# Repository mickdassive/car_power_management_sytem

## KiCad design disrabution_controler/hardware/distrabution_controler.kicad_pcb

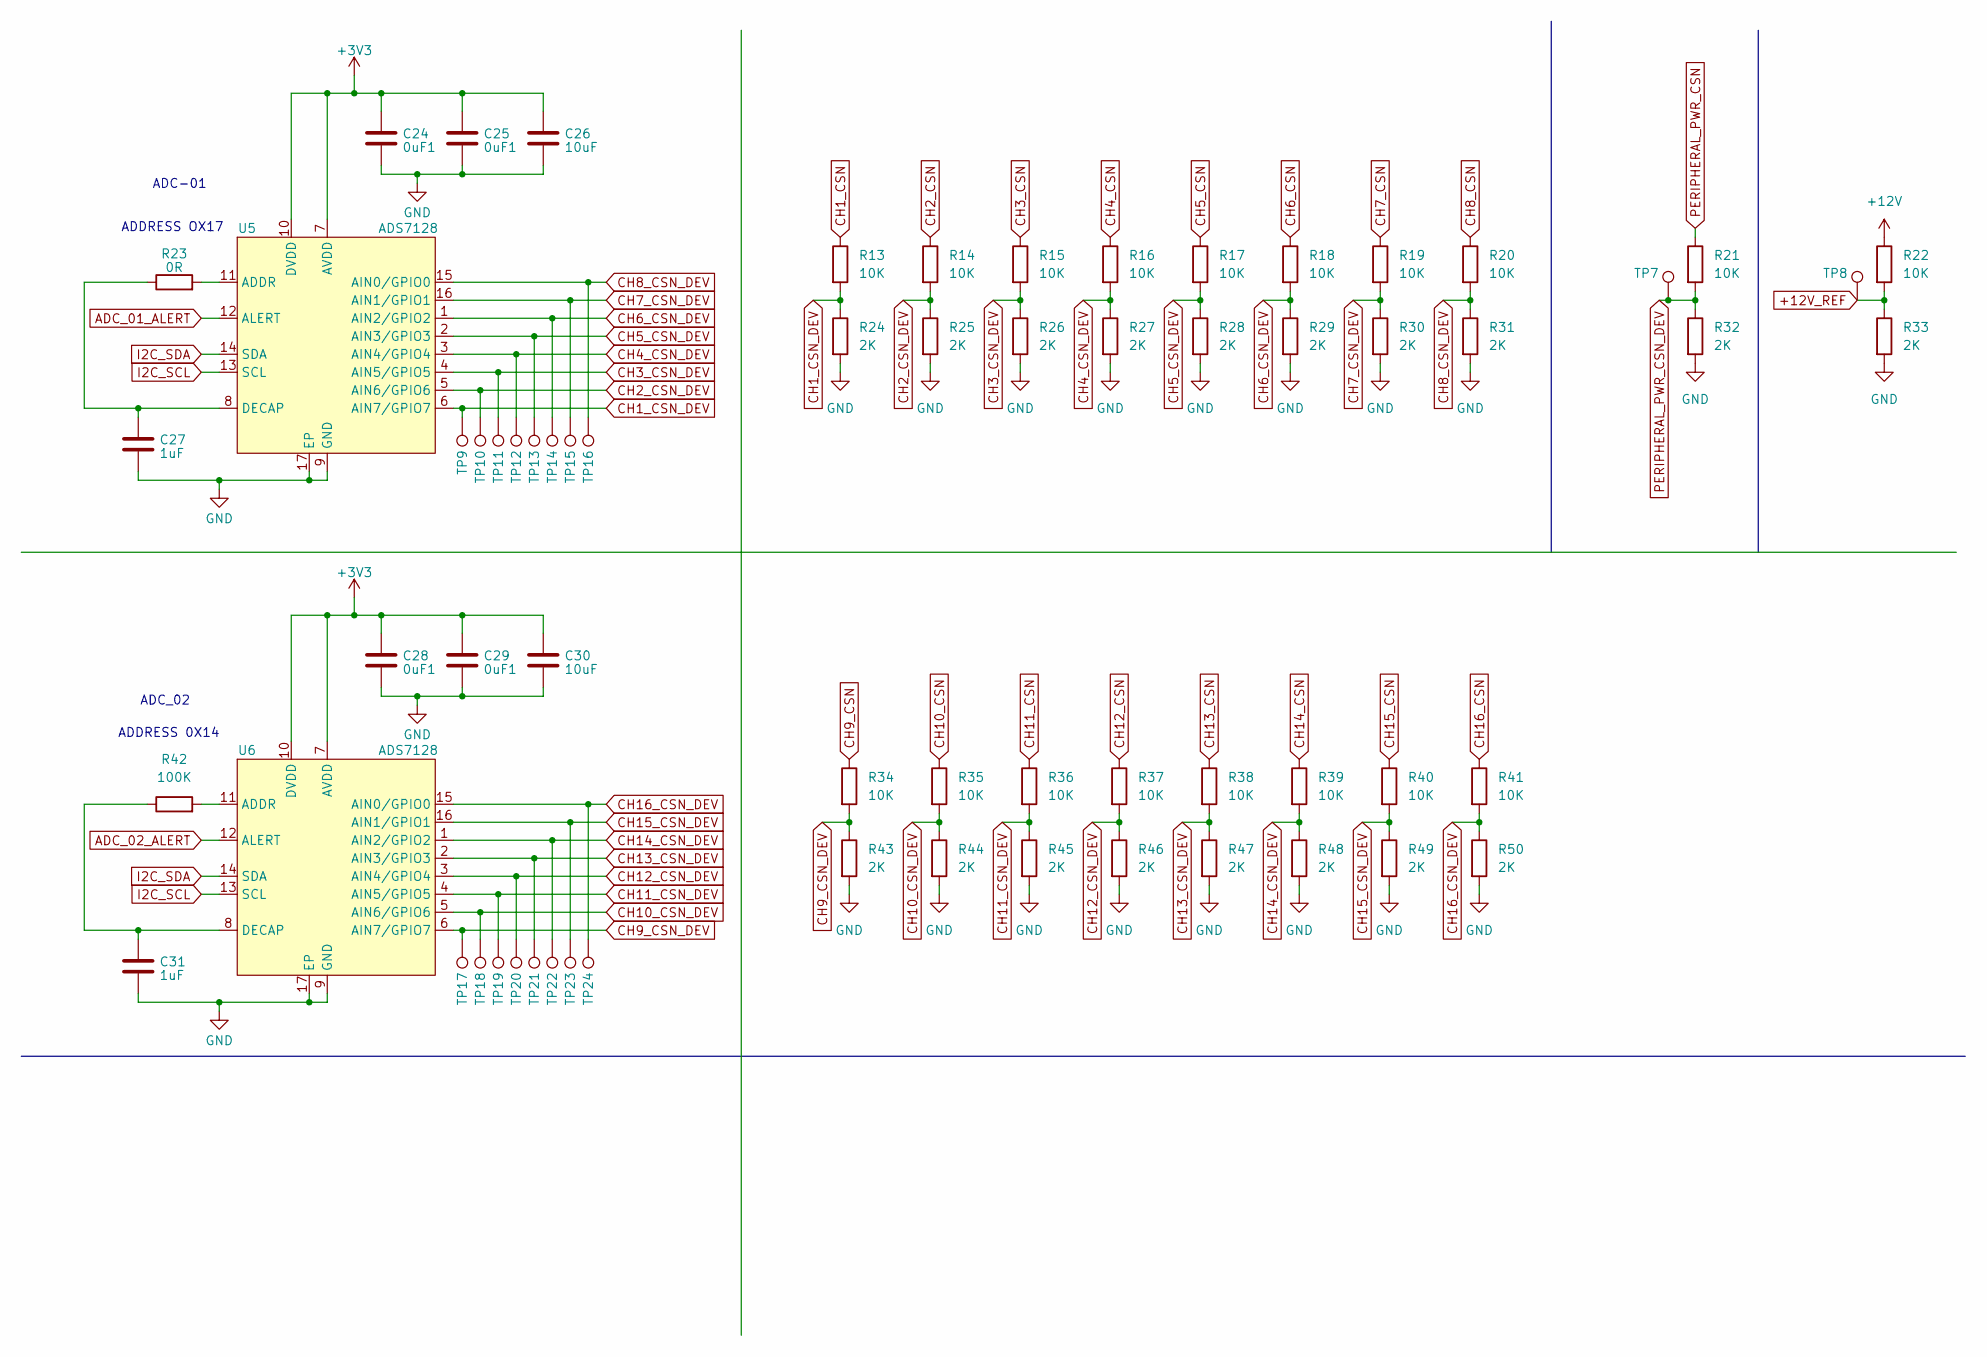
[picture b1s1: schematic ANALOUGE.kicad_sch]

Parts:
C24, C25, C28, C29: 0uF1; C_0603_1608Metric; Digikey Part Number 399-C0603C104M5RACTUCT-ND
C26, C30: 10uF; C_0603_1608Metric; Digikey Part Number 1276-1038-1-ND
C27, C31: 1uF; C_0603_1608Metric; Digikey Part Number 1276-1946-1-ND
R13, R14, R15, R16, R17, R18, R19, R20, R21, R22, R34, R35, R36, R37, R38, R39, R40, R41: 10K; R_0603_1608Metric; Digikey Part Number RMCF0603JT10K0CT-ND
R23: 0R; R_0603_1608Metric; Digikey Part Number 541-0.0GCT-ND
R24, R25, R26, R27, R28, R29, R30, R31, R32, R33, R43, R44, R45, R46, R47, R48, R49, R50: 2K; R_0603_1608Metric; Digikey Part Number 311-20.0KHRCT-ND
R42: 100K; R_0603_1608Metric; Digikey Part Number 541-100KHCT-ND
TP7, TP8, TP9, TP10, TP11, TP12, TP13, TP14, TP15, TP16, TP17, TP18, TP19, TP20, TP21, TP22, TP23, TP24: TestPoint_Pad_D1.0mm
U5, U6: ADS7128; WQFN-16-1EP_3x3mm_P0.5mm_EP1.6x1.6mm_ThermalVias; Digikey Part Number 296-ADS7128IRTERCT-ND

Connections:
+3V3: C24.1, C25.1, C26.1, C28.1, C29.1, C30.1, U5.7 (AVDD), U5.10 (DVDD), U6.7 (AVDD), U6.10 (DVDD); also elsewhere on the board
+12V: R22.1; also elsewhere on the board
+12V_REF: R22.2, R33.1, TP8.1; also elsewhere on the board
ADC_01_ALERT: U5.12 (ALERT); also elsewhere on the board
ADC_02_ALERT: U6.12 (ALERT); also elsewhere on the board
CH1_CSN: R13.1; also elsewhere on the board
CH1_CSN_DEV: R13.2, R24.1, TP9.1, U5.6 (AIN7/GPIO7)
CH2_CSN: R14.1; also elsewhere on the board
CH2_CSN_DEV: R14.2, R25.1, TP10.1, U5.5 (AIN6/GPIO6)
CH3_CSN: R15.1; also elsewhere on the board
CH3_CSN_DEV: R15.2, R26.1, TP11.1, U5.4 (AIN5/GPIO5)
CH4_CSN: R16.1; also elsewhere on the board
CH4_CSN_DEV: R16.2, R27.1, TP12.1, U5.3 (AIN4/GPIO4)
CH5_CSN: R17.1; also elsewhere on the board
CH5_CSN_DEV: R17.2, R28.1, TP13.1, U5.2 (AIN3/GPIO3)
CH6_CSN: R18.1; also elsewhere on the board
CH6_CSN_DEV: R18.2, R29.1, TP14.1, U5.1 (AIN2/GPIO2)
CH7_CSN: R19.1; also elsewhere on the board
CH7_CSN_DEV: R19.2, R30.1, TP15.1, U5.16 (AIN1/GPIO1)
CH8_CSN: R20.1; also elsewhere on the board
CH8_CSN_DEV: R20.2, R31.1, TP16.1, U5.15 (AIN0/GPIO0)
CH9_CSN: R34.1; also elsewhere on the board
CH9_CSN_DEV: R34.2, R43.1, TP17.1, U6.6 (AIN7/GPIO7)
CH10_CSN: R35.1; also elsewhere on the board
CH10_CSN_DEV: R35.2, R44.1, TP18.1, U6.5 (AIN6/GPIO6)
CH11_CSN: R36.1; also elsewhere on the board
CH11_CSN_DEV: R36.2, R45.1, TP19.1, U6.4 (AIN5/GPIO5)
CH12_CSN: R37.1; also elsewhere on the board
CH12_CSN_DEV: R37.2, R46.1, TP20.1, U6.3 (AIN4/GPIO4)
CH13_CSN: R38.1; also elsewhere on the board
CH13_CSN_DEV: R38.2, R47.1, TP21.1, U6.2 (AIN3/GPIO3)
CH14_CSN: R39.1; also elsewhere on the board
CH14_CSN_DEV: R39.2, R48.1, TP22.1, U6.1 (AIN2/GPIO2)
CH15_CSN: R40.1; also elsewhere on the board
CH15_CSN_DEV: R40.2, R49.1, TP23.1, U6.16 (AIN1/GPIO1)
CH16_CSN: R41.1; also elsewhere on the board
CH16_CSN_DEV: R41.2, R50.1, TP24.1, U6.15 (AIN0/GPIO0)
GND: C24.2, C25.2, C26.2, C27.2, C28.2, C29.2, C30.2, C31.2, R24.2, R25.2, R26.2, R27.2, R28.2, R29.2, R30.2, R31.2, R32.2, R33.2, R43.2, R44.2, R45.2, R46.2, R47.2, R48.2, R49.2, R50.2, U5.9 (GND), U5.17 (EP), U6.9 (GND), U6.17 (EP); also elsewhere on the board
I2C_SCL: U5.13 (SCL), U6.13 (SCL); also elsewhere on the board
I2C_SDA: U5.14 (SDA), U6.14 (SDA); also elsewhere on the board
unnamed: R23.2, U5.11 (ADDR)
unnamed: C27.1, R23.1, U5.8 (DECAP)
unnamed: R42.2, U6.11 (ADDR)
unnamed: C31.1, R42.1, U6.8 (DECAP)
PERIPHERAL_PWR_CSN: R21.1; also elsewhere on the board
PERIPHERAL_PWR_CSN_DEV: R21.2, R32.1, TP7.1; also elsewhere on the board

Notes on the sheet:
ADDRESS OX17
ADC_02
ADC-01
ADDRESS 0X14

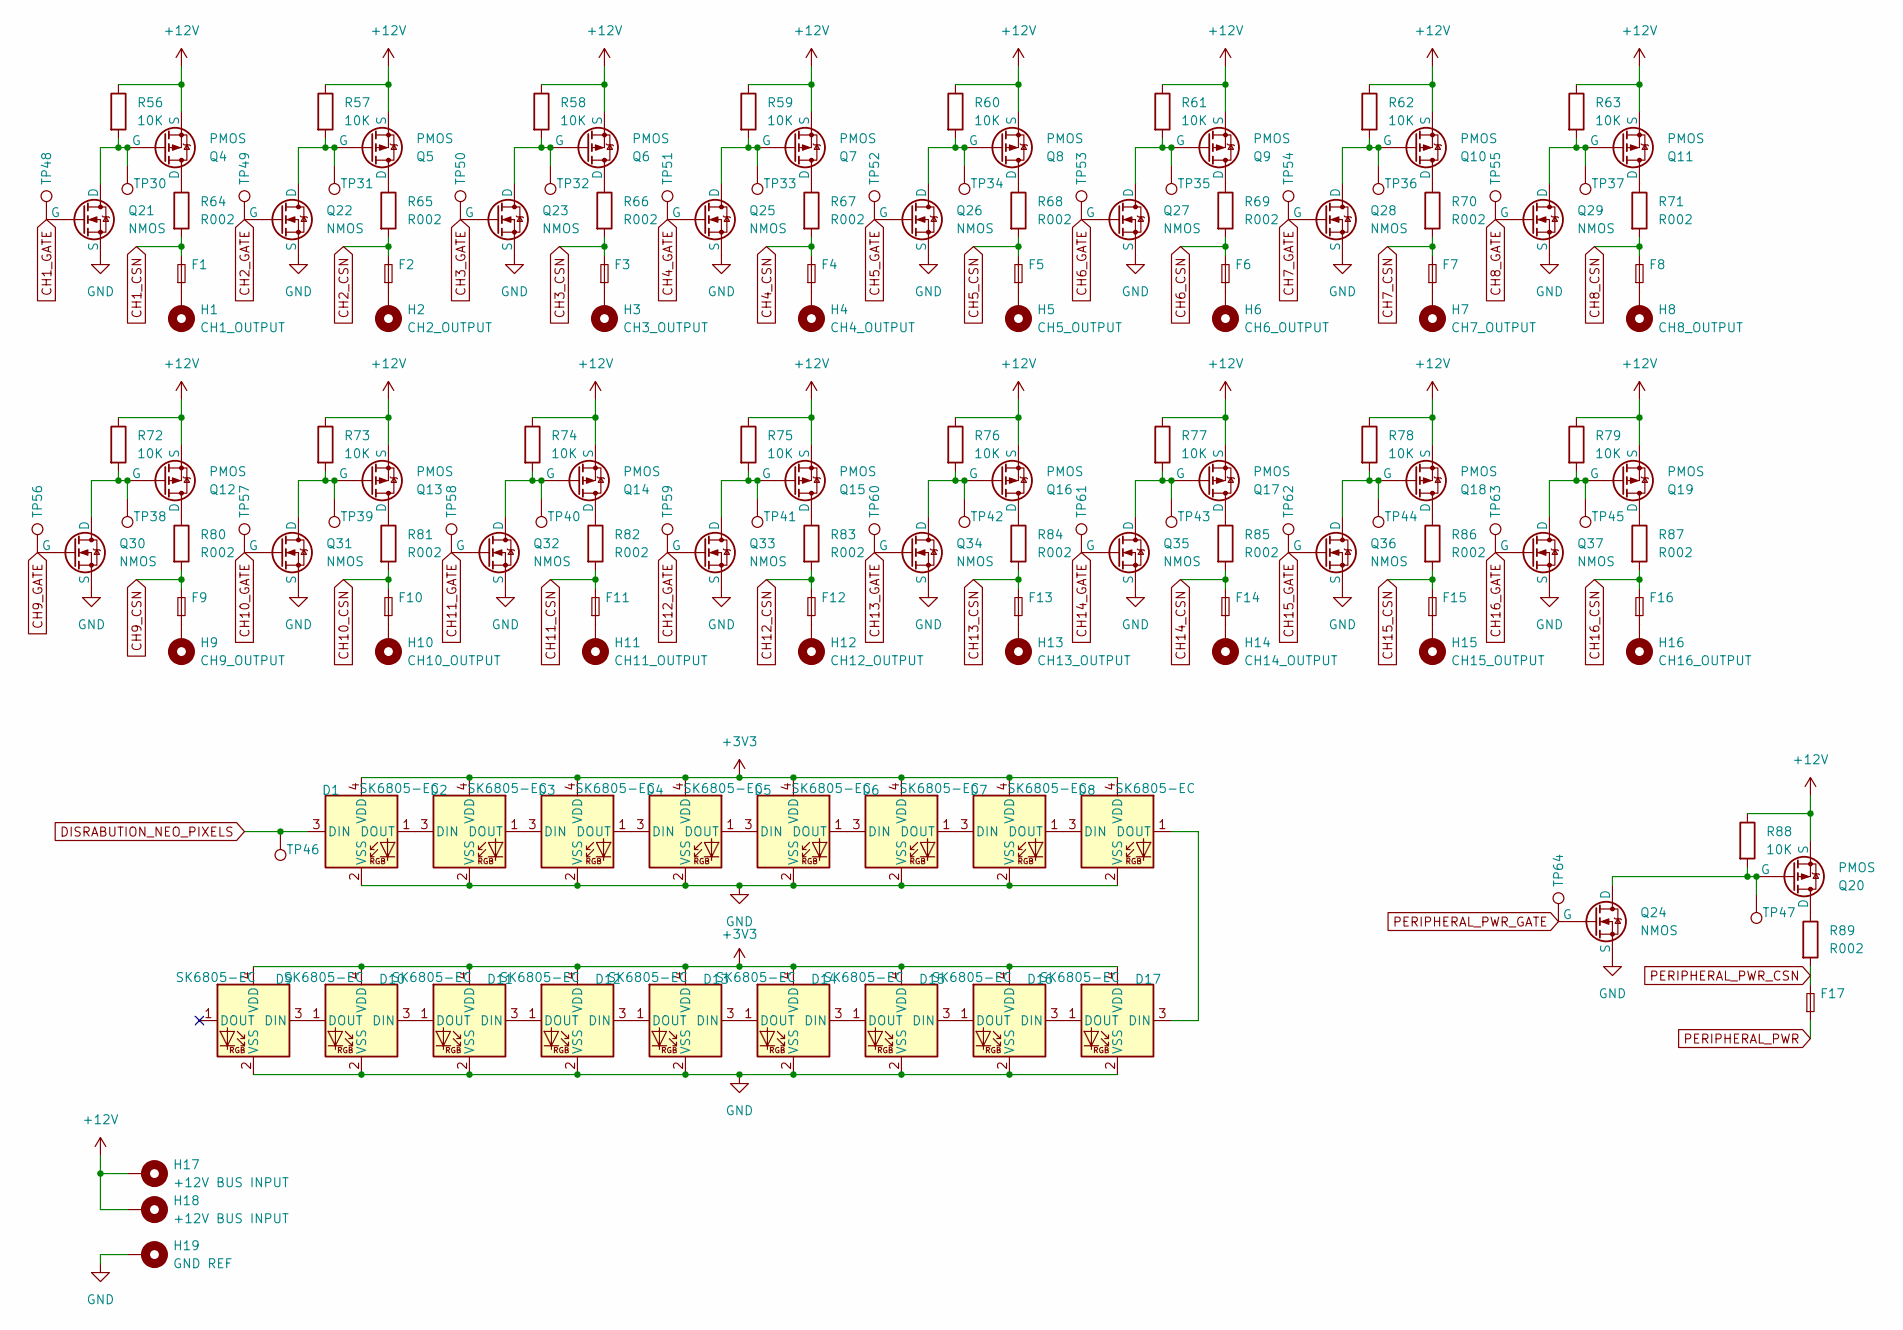
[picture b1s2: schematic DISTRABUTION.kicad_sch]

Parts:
D1, D2, D3, D4, D5, D6, D7, D8, D9, D10, D11, D12, D13, D14, D15, D16, D17: SK6805-EC; LED_SK6805_PLCC4_2.4x2.7mm_P1.3mm; Digikey Part Number 1528-4492-ND
F1, F2, F3, F4, F5, F6, F7, F8, F9, F10, F11, F12, F13, F14, F15, F16, F17: ATO_FUSEHOLDER; Digikey Part Number 36-3522-ND
H1: CH1_OUTPUT; MountingHole_6.4mm_M6_Pad_TopOnly
H2: CH2_OUTPUT; MountingHole_6.4mm_M6_Pad_TopOnly
H3: CH3_OUTPUT; MountingHole_6.4mm_M6_Pad_TopOnly
H4: CH4_OUTPUT; MountingHole_6.4mm_M6_Pad_TopOnly
H5: CH5_OUTPUT; MountingHole_6.4mm_M6_Pad_TopOnly
H6: CH6_OUTPUT; MountingHole_6.4mm_M6_Pad_TopOnly
H7: CH7_OUTPUT; MountingHole_6.4mm_M6_Pad_TopOnly
H8: CH8_OUTPUT; MountingHole_6.4mm_M6_Pad_TopOnly
H9: CH9_OUTPUT; MountingHole_6.4mm_M6_Pad_TopOnly
H10: CH10_OUTPUT; MountingHole_6.4mm_M6_Pad_TopOnly
H11: CH11_OUTPUT; MountingHole_6.4mm_M6_Pad_TopOnly
H12: CH12_OUTPUT; MountingHole_6.4mm_M6_Pad_TopOnly
H13: CH13_OUTPUT; MountingHole_6.4mm_M6_Pad_TopOnly
H14: CH14_OUTPUT; MountingHole_6.4mm_M6_Pad_TopOnly
H15: CH15_OUTPUT; MountingHole_6.4mm_M6_Pad_TopOnly
H16: CH16_OUTPUT; MountingHole_6.4mm_M6_Pad_TopOnly
H17, H18: +12V BUS INPUT; MountingHole_8.4mm_M8_Pad_TopOnly
H19: GND REF; MountingHole_6.4mm_M6_Pad_TopOnly
Q4, Q5, Q6, Q7, Q8, Q9, Q10, Q11, Q12, Q13, Q14, Q15, Q16, Q17, Q18, Q19, Q20: PMOS; Vishay_PowerPAK_1212-8_Single; Digikey Part Number SISS27DN-T1-GE3CT-ND
Q21, Q22, Q23, Q24, Q25, Q26, Q27, Q28, Q29, Q30, Q31, Q32, Q33, Q34, Q35, Q36, Q37: NMOS; SOT-23; Digikey Part Number BSS127H6327XTSA2CT-ND
R56, R57, R58, R59, R60, R61, R62, R63, R72, R73, R74, R75, R76, R77, R78, R79, R88: 10K; R_0603_1608Metric; Digikey Part Number RMCF0603JT10K0CT-ND
R64, R65, R66, R67, R68, R69, R70, R71, R80, R81, R82, R83, R84, R85, R86, R87, R89: R002; R_2512_6332Metric; Digikey Part Number CRF2512-FZ-R002ELFCT-ND
TP30, TP31, TP32, TP33, TP34, TP35, TP36, TP37, TP38, TP39, TP40, TP41, TP42, TP43, TP44, TP45, TP46, TP47, TP48, TP49, TP50, TP51, TP52, TP53, TP54, TP55, TP56, TP57, TP58, TP59, TP60, TP61, TP62, TP63, TP64: TestPoint_Pad_D1.0mm

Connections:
+3V3: D1.4 (VDD), D2.4 (VDD), D3.4 (VDD), D4.4 (VDD), D5.4 (VDD), D6.4 (VDD), D7.4 (VDD), D8.4 (VDD), D9.4 (VDD), D10.4 (VDD), D11.4 (VDD), D12.4 (VDD), D13.4 (VDD), D14.4 (VDD), D15.4 (VDD), D16.4 (VDD), D17.4 (VDD); also elsewhere on the board
+12V: H17.1, H18.1, Q4.1 (S), Q4.2 (S), Q4.3 (S), Q5.1 (S), Q5.2 (S), Q5.3 (S), Q6.1 (S), Q6.2 (S), Q6.3 (S), Q7.1 (S), Q7.2 (S), Q7.3 (S), Q8.1 (S), Q8.2 (S), Q8.3 (S), Q9.1 (S), Q9.2 (S), Q9.3 (S), Q10.1 (S), Q10.2 (S), Q10.3 (S), Q11.1 (S), Q11.2 (S), Q11.3 (S), Q12.1 (S), Q12.2 (S), Q12.3 (S), Q13.1 (S), Q13.2 (S), Q13.3 (S), Q14.1 (S), Q14.2 (S), Q14.3 (S), Q15.1 (S), Q15.2 (S), Q15.3 (S), Q16.1 (S), Q16.2 (S), Q16.3 (S), Q17.1 (S), Q17.2 (S), Q17.3 (S), Q18.1 (S), Q18.2 (S), Q18.3 (S), Q19.1 (S), Q19.2 (S), Q19.3 (S), Q20.1 (S), Q20.2 (S), Q20.3 (S), R56.1, R57.1, R58.1, R59.1, R60.1, R61.1, R62.1, R63.1, R72.1, R73.1, R74.1, R75.1, R76.1, R77.1, R78.1, R79.1, R88.1; also elsewhere on the board
CH1_CSN: F1.2, R64.2; also elsewhere on the board
CH1_GATE: Q21.1 (G), TP48.1; also elsewhere on the board
CH2_CSN: F2.2, R65.2; also elsewhere on the board
CH2_GATE: Q22.1 (G), TP49.1; also elsewhere on the board
CH3_CSN: F3.2, R66.2; also elsewhere on the board
CH3_GATE: Q23.1 (G), TP50.1; also elsewhere on the board
CH4_CSN: F4.2, R67.2; also elsewhere on the board
CH4_GATE: Q25.1 (G), TP51.1; also elsewhere on the board
CH5_CSN: F5.2, R68.2; also elsewhere on the board
CH5_GATE: Q26.1 (G), TP52.1; also elsewhere on the board
CH6_CSN: F6.2, R69.2; also elsewhere on the board
CH6_GATE: Q27.1 (G), TP53.1; also elsewhere on the board
CH7_CSN: F7.2, R70.2; also elsewhere on the board
CH7_GATE: Q28.1 (G), TP54.1; also elsewhere on the board
CH8_CSN: F8.2, R71.2; also elsewhere on the board
CH8_GATE: Q29.1 (G), TP55.1; also elsewhere on the board
CH9_CSN: F9.2, R80.2; also elsewhere on the board
CH9_GATE: Q30.1 (G), TP56.1; also elsewhere on the board
CH10_CSN: F10.2, R81.2; also elsewhere on the board
CH10_GATE: Q31.1 (G), TP57.1; also elsewhere on the board
CH11_CSN: F11.2, R82.2; also elsewhere on the board
CH11_GATE: Q32.1 (G), TP58.1; also elsewhere on the board
CH12_CSN: F12.2, R83.2; also elsewhere on the board
CH12_GATE: Q33.1 (G), TP59.1; also elsewhere on the board
CH13_CSN: F13.2, R84.2; also elsewhere on the board
CH13_GATE: Q34.1 (G), TP60.1; also elsewhere on the board
CH14_CSN: F14.2, R85.2; also elsewhere on the board
CH14_GATE: Q35.1 (G), TP61.1; also elsewhere on the board
CH15_CSN: F15.2, R86.2; also elsewhere on the board
CH15_GATE: Q36.1 (G), TP62.1; also elsewhere on the board
CH16_CSN: F16.2, R87.2; also elsewhere on the board
CH16_GATE: Q37.1 (G), TP63.1; also elsewhere on the board
DISRABUTION_NEO_PIXELS: D1.3 (DIN), TP46.1; also elsewhere on the board
GND: D1.2 (VSS), D2.2 (VSS), D3.2 (VSS), D4.2 (VSS), D5.2 (VSS), D6.2 (VSS), D7.2 (VSS), D8.2 (VSS), D9.2 (VSS), D10.2 (VSS), D11.2 (VSS), D12.2 (VSS), D13.2 (VSS), D14.2 (VSS), D15.2 (VSS), D16.2 (VSS), D17.2 (VSS), H19.1, Q21.2 (S), Q22.2 (S), Q23.2 (S), Q24.2 (S), Q25.2 (S), Q26.2 (S), Q27.2 (S), Q28.2 (S), Q29.2 (S), Q30.2 (S), Q31.2 (S), Q32.2 (S), Q33.2 (S), Q34.2 (S), Q35.2 (S), Q36.2 (S), Q37.2 (S); also elsewhere on the board
unnamed: D1.1 (DOUT), D2.3 (DIN)
unnamed: D2.1 (DOUT), D3.3 (DIN)
unnamed: D3.1 (DOUT), D4.3 (DIN)
unnamed: D4.1 (DOUT), D5.3 (DIN)
unnamed: D5.1 (DOUT), D6.3 (DIN)
unnamed: D6.1 (DOUT), D7.3 (DIN)
unnamed: D7.1 (DOUT), D8.3 (DIN)
unnamed: D10.3 (DIN), D11.1 (DOUT)
unnamed: D9.3 (DIN), D10.1 (DOUT)
unnamed: D11.3 (DIN), D12.1 (DOUT)
unnamed: D12.3 (DIN), D13.1 (DOUT)
unnamed: D13.3 (DIN), D14.1 (DOUT)
unnamed: D14.3 (DIN), D15.1 (DOUT)
unnamed: D15.3 (DIN), D16.1 (DOUT)
unnamed: D16.3 (DIN), D17.1 (DOUT)
unnamed: D8.1 (DOUT), D17.3 (DIN)
unnamed: F1.1, H1.1
unnamed: F2.1, H2.1
unnamed: F3.1, H3.1
unnamed: F4.1, H4.1
unnamed: F5.1, H5.1
unnamed: F6.1, H6.1
unnamed: F7.1, H7.1
unnamed: F8.1, H8.1
unnamed: F9.1, H9.1
unnamed: F10.1, H10.1
unnamed: F11.1, H11.1
unnamed: F12.1, H12.1
unnamed: F13.1, H13.1
unnamed: F14.1, H14.1
unnamed: F15.1, H15.1
unnamed: F16.1, H16.1
unnamed: Q4.5 (D), R64.1
unnamed: Q5.5 (D), R65.1
unnamed: Q6.5 (D), R66.1
unnamed: Q7.5 (D), R67.1
unnamed: Q8.5 (D), R68.1
unnamed: Q9.5 (D), R69.1
unnamed: Q10.5 (D), R70.1
unnamed: Q10.4 (G), Q28.3 (D), R62.2, TP36.1
unnamed: Q11.5 (D), R71.1
unnamed: Q11.4 (G), Q29.3 (D), R63.2, TP37.1
unnamed: Q12.5 (D), R80.1
unnamed: Q12.4 (G), Q30.3 (D), R72.2, TP38.1
unnamed: Q13.5 (D), R81.1
unnamed: Q13.4 (G), Q31.3 (D), R73.2, TP39.1
unnamed: Q14.5 (D), R82.1
unnamed: Q14.4 (G), Q32.3 (D), R74.2, TP40.1
unnamed: Q15.5 (D), R83.1
unnamed: Q15.4 (G), Q33.3 (D), R75.2, TP41.1
unnamed: Q16.5 (D), R84.1
unnamed: Q16.4 (G), Q34.3 (D), R76.2, TP42.1
unnamed: Q17.5 (D), R85.1
unnamed: Q17.4 (G), Q35.3 (D), R77.2, TP43.1
unnamed: Q18.5 (D), R86.1
unnamed: Q18.4 (G), Q36.3 (D), R78.2, TP44.1
unnamed: Q19.5 (D), R87.1
unnamed: Q19.4 (G), Q37.3 (D), R79.2, TP45.1
unnamed: Q20.5 (D), R89.1
unnamed: Q20.4 (G), Q24.3 (D), R88.2, TP47.1
unnamed: Q4.4 (G), Q21.3 (D), R56.2, TP30.1
unnamed: Q5.4 (G), Q22.3 (D), R57.2, TP31.1
unnamed: Q6.4 (G), Q23.3 (D), R58.2, TP32.1
unnamed: Q7.4 (G), Q25.3 (D), R59.2, TP33.1
unnamed: Q8.4 (G), Q26.3 (D), R60.2, TP34.1
unnamed: Q9.4 (G), Q27.3 (D), R61.2, TP35.1
PERIPHERAL_PWR: F17.1; also elsewhere on the board
PERIPHERAL_PWR_CSN: F17.2, R89.2; also elsewhere on the board
PERIPHERAL_PWR_GATE: Q24.1 (G), TP64.1; also elsewhere on the board

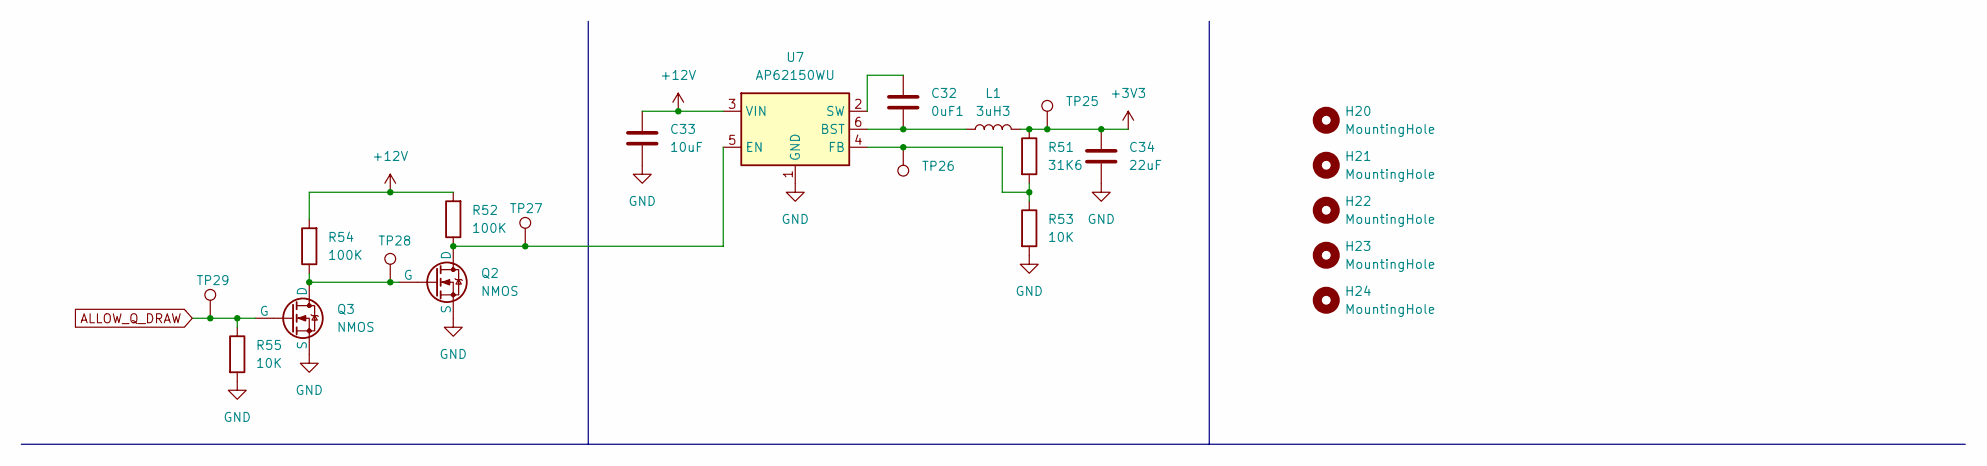
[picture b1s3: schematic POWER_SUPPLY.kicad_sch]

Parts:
C32: 0uF1; C_0603_1608Metric; Digikey Part Number 399-C0603C104M5RACTUCT-ND
C33: 10uF; C_0603_1608Metric; Digikey Part Number 1276-1038-1-ND
C34: 22uF; C_0603_1608Metric; Digikey Part Number 490-7611-1-ND
H20, H21, H22, H23, H24: MountingHole; MountingHole_4.3mm_M4
L1: 3uH3; L_Bourns_SDR0604; Digikey Part Number 445-173052-1-ND
Q2, Q3: NMOS; SOT-23; Digikey Part Number BSS127H6327XTSA2CT-ND
R51: 31K6; R_0603_1608Metric; Digikey Part Number 541-5351-1-ND
R52, R54: 100K; R_0603_1608Metric; Digikey Part Number 541-100KHCT-ND
R53, R55: 10K; R_0603_1608Metric; Digikey Part Number RMCF0603JT10K0CT-ND
TP25, TP26, TP27, TP28, TP29: TestPoint_Pad_D1.0mm
U7: AP62150WU; TSOT-23-6; Digikey Part Number 31-AP62150WU-7CT-ND

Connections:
+3V3: C34.1, L1.2, R51.1, TP25.1; also elsewhere on the board
+12V: C33.1, R52.2, R54.2, U7.3 (VIN); also elsewhere on the board
ALLOW_Q_DRAW: Q3.1 (G), R55.1, TP29.1; also elsewhere on the board
GND: C33.2, C34.2, Q2.2 (S), Q3.2 (S), R53.2, R55.2, U7.1 (GND); also elsewhere on the board
unnamed: Q2.3 (D), R52.1, TP27.1, U7.5 (EN)
unnamed: Q2.1 (G), Q3.3 (D), R54.1, TP28.1
unnamed: C32.2, L1.1, U7.6 (BST)
unnamed: R51.2, R53.1, TP26.1, U7.4 (FB)
unnamed: C32.1, U7.2 (SW)

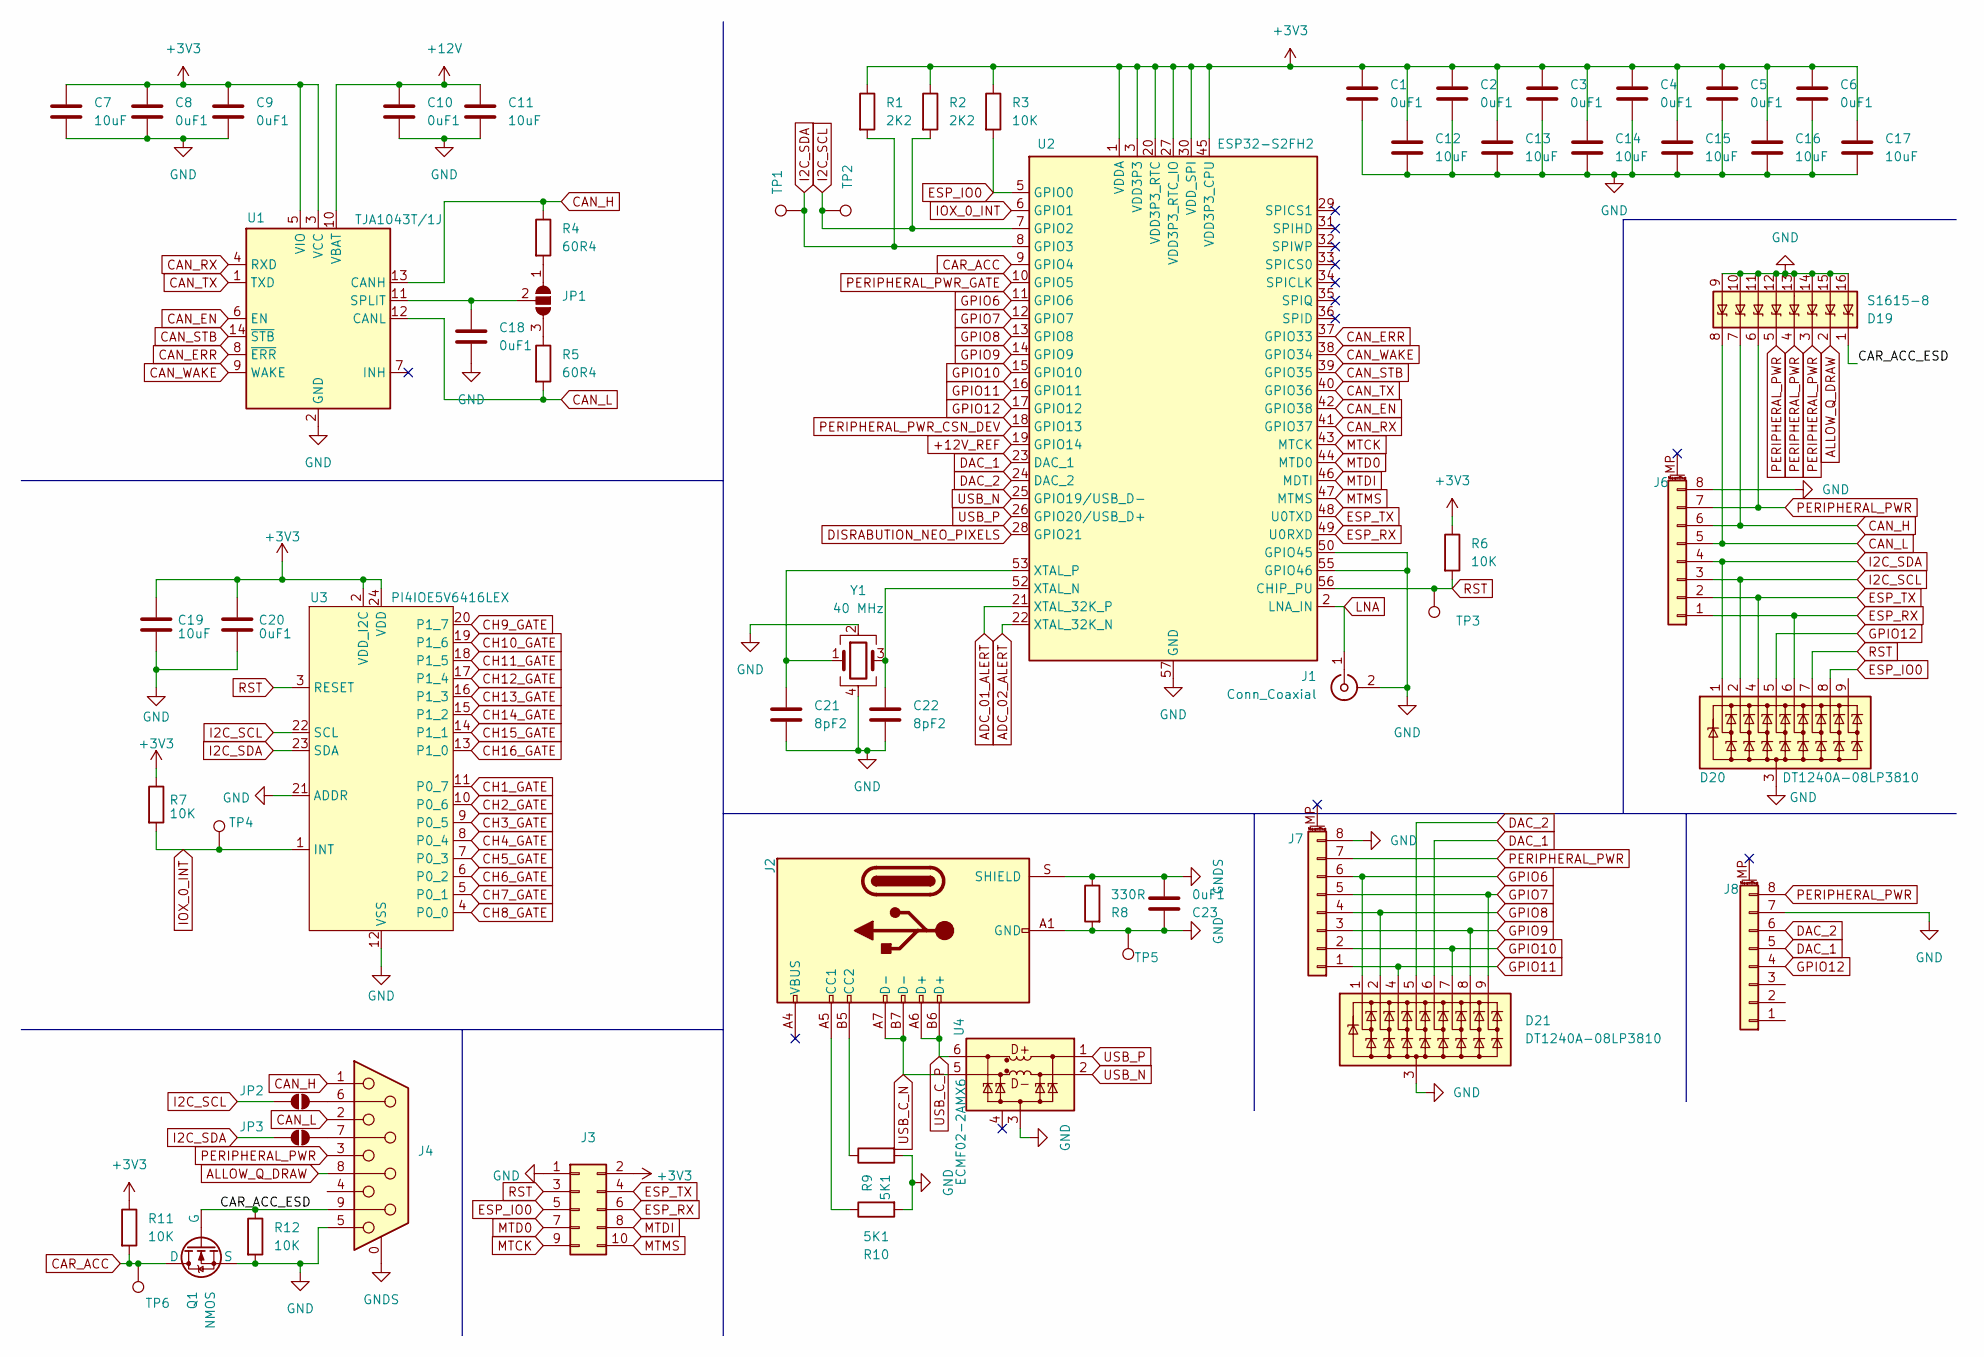
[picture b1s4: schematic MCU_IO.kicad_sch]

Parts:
C1, C2, C3, C4, C5, C6, C8, C9, C10, C18, C20, C23: 0uF1; C_0603_1608Metric; Digikey Part Number 399-C0603C104M5RACTUCT-ND
C7, C11, C12, C13, C14, C15, C16, C17, C19: 10uF; C_0603_1608Metric; Digikey Part Number 1276-1038-1-ND
C21, C22: 8pF2; C_0603_1608Metric; Digikey Part Number 4713-CHV0603N2508R2BCT-ND
D19: S1615-8; SO-16_5.3x10.2mm_P1.27mm
D20, D21: DT1240A-08LP3810; UDFN-9_1.0x3.8mm_P0.5mm
J1: Conn_Coaxial; SMA_Amphenol_132291-12_Vertical; Digikey Part Number CONREVSMA001-G-ND
J2: usb4500; Digikey Part Number 2073-USB4500-03-0-ACT-ND
J3: PinHeader_2x05_P2.54mm_Vertical; Digikey Part Number S9169-ND
J4: DSUB-9_Pins_Horizontal_P2.77x2.84mm_EdgePinOffset4.94mm_Hou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; Digikey Part Number AE10921-ND
J6, J7, J8: PhoenixContact_MC_1,5_8-GF-3.81_1x08_P3.81mm_Horizontal_Thr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
JP1: SolderJumper-3_P2.0mm_Open_TrianglePad1.0x1.5mm
JP2, JP3: SolderJumper-2_P1.3mm_Open_TrianglePad1.0x1.5mm
Q1: NMOS; SOT-23; Digikey Part Number BSS127H6327XTSA2CT-ND
R1, R2: 2K2; R_0603_1608Metric; Digikey Part Number 541-1.00KHCT-ND
R3, R6, R7, R11, R12: 10K; R_0603_1608Metric; Digikey Part Number RMCF0603JT10K0CT-ND
R4, R5: 60R4; R_0603_1608Metric; Digikey Part Number 541-5507-1-ND
R8: 330R; R_0603_1608Metric; Digikey Part Number 541-4026-1-ND
R9, R10: 5K1; R_0603_1608Metric; Digikey Part Number 541-4030-1-ND
TP1, TP2, TP3, TP4, TP5, TP6: TestPoint_Pad_D1.0mm
U1: TJA1043T/1J; SOIC-14_3.9x8.7mm_P1.27mm; Digikey Part Number 568-13274-1-ND
U2: ESP32-S2FH2; QFN-56-1EP_7x7mm_P0.4mm_EP4x4mm; Digikey Part Number 1904-ESP32-S2FH2CT-ND
U3: PI4IOE5V6416LEX; TSSOP-24_4.4x7.8mm_P0.65mm; Digikey Part Number PI4IOE5V6416LEXDICT-ND
U4: ECMF02-2AMX6; ST_UQFN-6L_1.5x1.7mm_P0.5mm; Digikey Part Number 497-10773-1-ND
Y1: 40 MHz; cx3225sa_e; Digikey Part Number 478-CX3225SA40000D0PTWCCCT-ND

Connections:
+3V3: C1.1, C2.1, C3.1, C4.1, C5.1, C6.1, C7.1, C8.1, C9.1, C12.1, C13.1, C14.1, C15.1, C16.1, C17.1, C19.1, C20.1, J3.2, R1.1, R2.1, R3.1, R6.1, R7.1, R11.1, U1.3 (VCC), U1.5 (VIO), U2.1 (VDDA), U2.3 (VDD3P3), U2.4 (VDD3P3), U2.20 (VDD3P3_RTC), U2.27 (VDD3P3_RTC_IO), U2.30 (VDD_SPI), U2.45 (VDD3P3_CPU), U2.51 (VDDA), U2.54 (VDDA), U3.2 (VDD_I2C), U3.24 (VDD); also elsewhere on the board
+12V: C10.1, C11.1, U1.10 (VBAT); also elsewhere on the board
+12V_REF: U2.19 (GPIO14); also elsewhere on the board
/MCU_IO/CAR_ACC_ESD: D19.1 (Line-1), J4.9, Q1.1 (G), R12.1
ADC_01_ALERT: U2.21 (XTAL_32K_P); also elsewhere on the board
ADC_02_ALERT: U2.22 (XTAL_32K_N); also elsewhere on the board
ALLOW_Q_DRAW: D19.2 (Line-3), J4.8; also elsewhere on the board
CAN_EN: U1.6 (EN), U2.42 (GPIO38)
CAN_ERR: U1.8 (~ERR), U2.37 (GPIO33)
CAN_H: D19.7 (Line-4), J4.1, J6.6, R4.1, U1.13 (CANH)
CAN_L: D19.8 (Line-2), J4.2, J6.5, R5.2, U1.12 (CANL)
CAN_RX: U1.4 (RXD), U2.41 (GPIO37)
CAN_STB: U1.14 (~STB), U2.39 (GPIO35)
CAN_TX: U1.1 (TXD), U2.40 (GPIO36)
CAN_WAKE: U1.9 (WAKE), U2.38 (GPIO34)
CAR_ACC: Q1.3 (D), R11.2, TP6.1, U2.9 (GPIO4)
CH1_GATE: U3.11 (P0_7); also elsewhere on the board
CH2_GATE: U3.10 (P0_6); also elsewhere on the board
CH3_GATE: U3.9 (P0_5); also elsewhere on the board
CH4_GATE: U3.8 (P0_4); also elsewhere on the board
CH5_GATE: U3.7 (P0_3); also elsewhere on the board
CH6_GATE: U3.6 (P0_2); also elsewhere on the board
CH7_GATE: U3.5 (P0_1); also elsewhere on the board
CH8_GATE: U3.4 (P0_0); also elsewhere on the board
CH9_GATE: U3.20 (P1_7); also elsewhere on the board
CH10_GATE: U3.19 (P1_6); also elsewhere on the board
CH11_GATE: U3.18 (P1_5); also elsewhere on the board
CH12_GATE: U3.17 (P1_4); also elsewhere on the board
CH13_GATE: U3.16 (P1_3); also elsewhere on the board
CH14_GATE: U3.15 (P1_2); also elsewhere on the board
CH15_GATE: U3.14 (P1_1); also elsewhere on the board
CH16_GATE: U3.13 (P1_0); also elsewhere on the board
DAC_1: D21.6 (K5), J8.5, U2.23 (DAC_1)
DAC_2: D21.5 (K4), J8.6, U2.24 (DAC_2)
DISRABUTION_NEO_PIXELS: U2.28 (GPIO21); also elsewhere on the board
ESP_IO0: D20.8 (K7), J3.5, R3.2, U2.5 (GPIO0)
ESP_RX: D20.6 (K5), J3.6, J6.1, U2.49 (U0RXD)
ESP_TX: D20.4 (K3), J3.4, J6.2, U2.48 (U0TXD)
GND: C1.2, C2.2, C3.2, C4.2, C5.2, C6.2, C7.2, C8.2, C9.2, C10.2, C11.2, C12.2, C13.2, C14.2, C15.2, C16.2, C17.2, C18.2, C19.2, C20.2, C21.2, C22.2, C23.2, D19.9 (Line-2), D19.10 (Line-4), D19.11, D19.12 (Line-7), D19.13 (Line-8), D19.14 (Line-6), D19.15 (Line-3), D19.16 (Line-1), D20.3 (A), D21.3 (A), J1.2 (Ext), J2.A1 (GND), J2.A12 (GND), J2.B1 (GND), J2.B12 (GND), J3.1, J4.5, J6.8, J7.8, J8.7, Q1.2 (S), R8.2, R9.2, R10.2, R12.2, TP5.1, U1.2 (GND), U2.50 (GPIO45), U2.55 (GPIO46), U2.57 (GND), U3.12 (VSS), U3.21 (ADDR), U4.3 (GND), Y1.2, Y1.4; also elsewhere on the board
GNDS: C23.1, J2.S (SHIELD), J4.0 (PAD), R8.1
GPIO6: D21.1 (K1), J7.6, U2.11 (GPIO6)
GPIO7: D21.9 (K8), J7.5, U2.12 (GPIO7)
GPIO8: D21.2 (K2), J7.4, U2.13 (GPIO8)
GPIO9: D21.8 (K7), J7.3, U2.14 (GPIO9)
GPIO10: D21.7 (K6), J7.2, U2.15 (GPIO10)
GPIO11: D21.4 (K3), J7.1, U2.16 (GPIO11)
GPIO12: D20.5 (K4), J8.4, U2.17 (GPIO12)
I2C_SCL: D20.2 (K2), J6.3, JP2.1 (A), R2.2, TP2.1, U2.7 (GPIO2), U3.22 (SCL); also elsewhere on the board
I2C_SDA: D20.1 (K1), J6.4, JP3.1 (A), R1.2, TP1.1, U2.8 (GPIO3), U3.23 (SDA); also elsewhere on the board
IOX_0_INT: R7.2, TP4.1, U2.6 (GPIO1), U3.1 (INT)
LNA: J1.1 (In), U2.2 (LNA_IN)
MTCK: J3.9, U2.43 (MTCK)
MTD0: J3.7, U2.44 (MTD0)
MTDI: J3.8, U2.46 (MDTI)
MTMS: J3.10, U2.47 (MTMS)
unnamed: J2.A5 (CC1), R10.1
unnamed: J2.B5 (CC2), R9.1
unnamed: JP1.1 (A), R4.2
unnamed: JP1.3 (B), R5.1
unnamed: C18.1, JP1.2 (C), U1.11 (SPLIT)
unnamed: J4.6, JP2.2 (B)
unnamed: J4.7, JP3.2 (B)
unnamed: C22.1, U2.52 (XTAL_N), Y1.3
unnamed: C21.1, U2.53 (XTAL_P), Y1.1
PERIPHERAL_PWR: D19.3 (Line-6), D19.4 (Line-8), D19.5 (Line-7), D19.6 (Line-5), J4.3, J6.7, J7.7, J8.8; also elsewhere on the board
PERIPHERAL_PWR_CSN_DEV: U2.18 (GPIO13); also elsewhere on the board
PERIPHERAL_PWR_GATE: U2.10 (GPIO5); also elsewhere on the board
RST: D20.7 (K6), J3.3, R6.2, TP3.1, U2.56 (CHIP_PU), U3.3 (RESET)
USB_C_N: J2.A7 (D-), J2.B7 (D-), U4.5 (D-_out)
USB_C_P: J2.A6 (D+), J2.B6 (D+), U4.6 (D+_out)
USB_N: U2.25 (GPIO19/USB_D-), U4.2 (D-_in)
USB_P: U2.26 (GPIO20/USB_D+), U4.1 (D+_in)

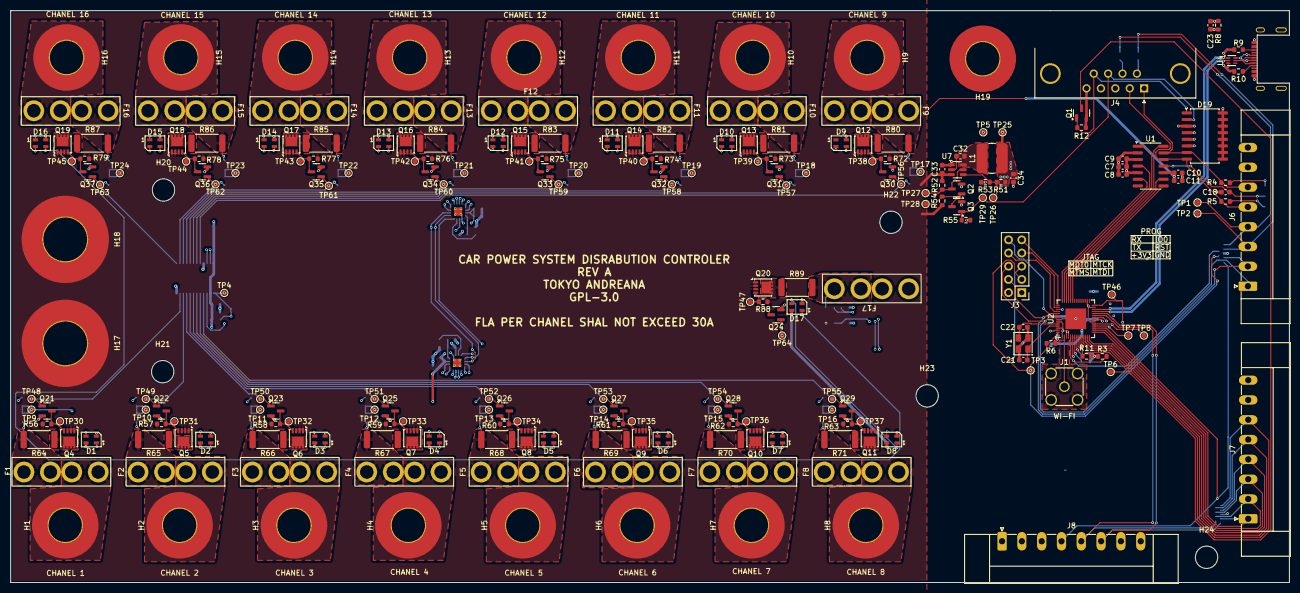
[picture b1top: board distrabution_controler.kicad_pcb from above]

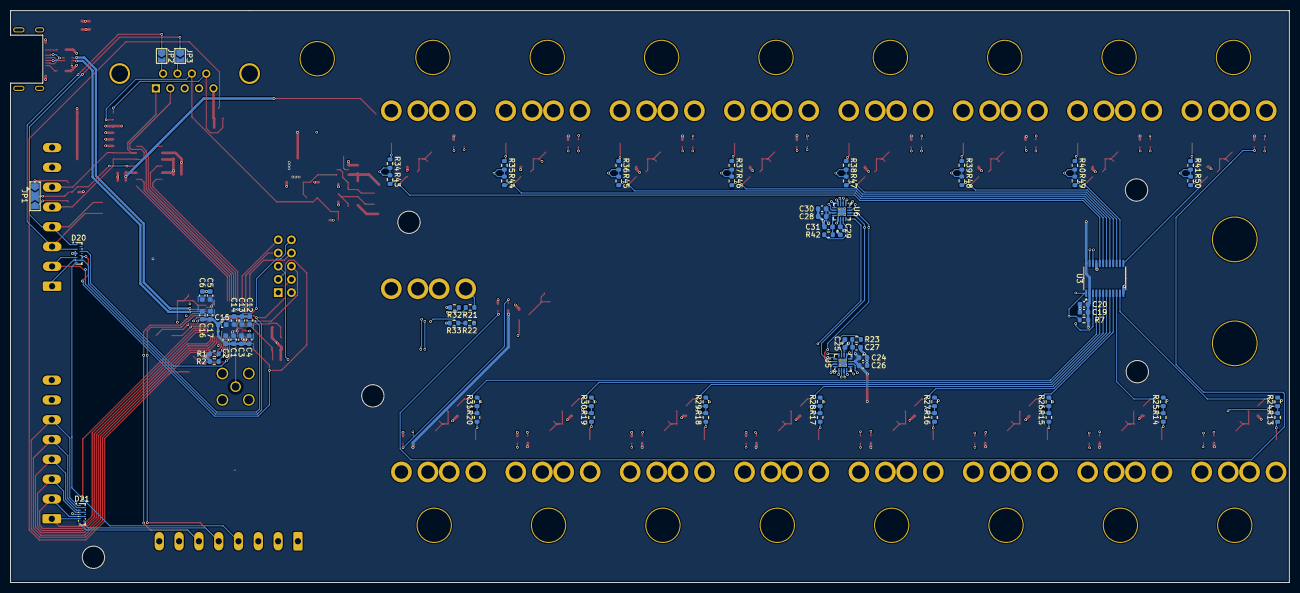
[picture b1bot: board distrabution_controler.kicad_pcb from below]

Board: 4 copper layers, 246.0 x 110.0 mm, 304 parts (71 on the bottom side), 180 nets.

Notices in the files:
disrabution_controler/src/io.h:
Copyright (C) {2023}  {mickmake}
This program is free software: you can redistribute it and/or modify
it under the terms of the GNU General Public License as published by
the Free Software Foundation, either version 3 of the License.
disrabution_controler/hardware/distrabution_controler.kicad_pcb:
GPL-3.0
